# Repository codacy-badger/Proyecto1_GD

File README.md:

<p align="center"><p>

&nbsp;&nbsp;&nbsp;&nbsp;&nbsp;&nbsp;&nbsp;&nbsp;&nbsp;&nbsp;&nbsp;&nbsp;&nbsp;&nbsp;&nbsp;&nbsp;&nbsp;&nbsp;&nbsp;&nbsp;&nbsp;&nbsp;&nbsp;&nbsp;&nbsp;&nbsp;&nbsp;&nbsp;&nbsp;

&nbsp;&nbsp;&nbsp;&nbsp;&nbsp;&nbsp;&nbsp;&nbsp;&nbsp;&nbsp;&nbsp;&nbsp;&nbsp;&nbsp;&nbsp;&nbsp;&nbsp;&nbsp;&nbsp;&nbsp;&nbsp;&nbsp;&nbsp;&nbsp;&nbsp;&nbsp;&nbsp;&nbsp;&nbsp;&nbsp;&nbsp;&nbsp;&nbsp;

<!--  -->

# Proyecto1_GD
Proyecto en desarrollo, a continuación se describen las carpetas incluidas en el proyecto:

```
Proyecto1_GD
| .gitignore
| CONTRIBUTING.md
| LICENSE.md
| Manual.md
| README.md
|-- Archivos
|-- PlayGround
|-- Proyecto_A
|-- Proyecto_B
|-- Proyecto_C
|-- Proyecto_GUI
|-- Recursos
    |-- audio
    |-- imagenes
```

### 1. Archivos
Aqui incluiremos todos los archivos que aporten documentación al desarrollo, todos los archivos con formato *.docx* o *.pdf* dentro de la carpeta correspondiente al proyecto.

### 2.  PlayGround
Aqui cada uno puede incluir programas de prueba o borradores dentro de su carpeta correspondiente. Estos programas no pertenecen a la versión final del proyecto.

### 3. Proyecto A
Aquí incluiremos todo lo relacionado al desarrollo del [Proyecto A](./Proyecto_A), código, fichas técnicas y planos.

### 4. Proyecto B
Aquí incluiremos todo lo relacionado al desarrollo del Proyecto B, código, fichas técnicas y planos.
Este proyecto aún no esta definido.

### 5. Proyecto C
Aquí incluiremos todo lo relacionado al desarrollo del Proyecto C, código, fichas técnicas y planos.
Este proyecto aún no esta definido.

### 6. Proyecto GUI
Desarrollo de un Interfaz Gráfico.

#### Recursos
Aquí incluiremos principalmente imágenes de apoyo para las descripciones adicionales en los archivos README.md.

#### Extras
- Manual de uso [aquí](./Manual.md).
- Pautas de contribuyente [aquí](./CONTRIBUTING.md).

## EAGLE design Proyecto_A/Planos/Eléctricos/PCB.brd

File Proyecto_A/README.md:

<p align="center"><p>

# Proyecto A

```
|-- Proyecto_A
    |-- ADXL362
    |-- BMA400
    |-- Fichas_Técnicas
    |-- Planos
        |-- Mecánicos
        |-- Eléctricos
    |-- XBee
```

## Descripción

#### Sensores
- ADXL362 (MEMS Acelerómetro)
- BMA400 (Acelerómetro - BOSCH)
- MPU6050 (3 Acelerómetros y 3 giróscopos)

#### Microcontrolador (uC)
- MSP430 - Texas Instruments

#### Transmisor Tx/Rx
- XBee

#### Sensor x *N*

## 1. Fichas Técnicas
En esta carpeta podemos guardar todas las fichas técnicas relacionadas al proyecto.

## 2. Planos
En esta carpeta, se debe tener separado los planos mecánicos y eléctricos relacionados al proyecto. Incluir todos los planos sobre un mismo elemento dentro de una carpeta e incluir una descripción breve del contenido en un archivo MarkDown(.md)

#### 1. Mecánicos
Planos del encapsulado para los elementos electrónicos.

#### 2. Eléctricos
Planos del circuito impreso (PCB).
- Placa A
- Placa B

- uC+Xbee+MPU6050
- Modelo ATMEGA328P-AU+MPU+XBEE3: 20mm*28mm
<p align="center"><p>

- ATMEGA328P-AU+MPU6050+XBEE3, Size: 20mm*28mm
<p align="center"><p>

- ATMEGA328P-MU+MPU+XBEE3: Size: 21mm*27mm
<p align="center">

<p>

- MPU+XBEE3: Size: 18mm*28mm
<p align="center">

<p>

- 1: PCB: ADXLE362 [SPI] + uC + XBee3
- 2: PCB: BMA400 [I2C] + uC + XBee3
- 3: PCB: BMI270 [I2C] + uC + XBee3

#### Ubicación de los sensores
Las medidas de la cavidad donde iría el circuito es de 15mmx7mm y la profundidad es de 20mm.
<p align="center"><p>
<p align="center"><p>

En la siguiente foto se muestra el Xbee3 junto con su antena en una cavidad.
<p align="center"><p>

##### Sensores
- [Sensores de Vibración](https://faire-ca-soi-meme.fr/domotique/2018/09/03/test-xiaomi-aqara-vibration-sensor/)
- [Sensor de Humedad](https://faire-ca-soi-meme.fr/hack/2017/02/27/hack-xiaomi-mi-smart-temperature-and-humidity-sensor/)
- [MSP430](http://www.ti.com/product/MSP430G2553/technicaldocuments)
- [MSP-EXP43G2](https://www.mouser.pe/ProductDetail/Texas-Instruments/MSP-EXP430G2?qs=CLImetaeaXWH2pYG%252BA%252B4Vw%3D%3D)
- [MIKROE-3149](https://www.mouser.pe/ProductDetail/Mikroe/MIKROE-3149?qs=sGAEpiMZZMve4%2FbfQkoj%252BEPi4ApqHNF8CEaaCJoKqNM%3D)
- [BMA400](https://ae-bst.resource.bosch.com/media/_tech/media/datasheets/BST-BMA400-DS000.pdf)

##### Baterías
- [Li-Po Battery 3.7V 100mAh](https://es.aliexpress.com/item/4000670261171.html?spm=a2g0o.productlist.0.0.361999f3FETcJP&algo_pvid=44eadfe1-7417-4d6e-ab31-6dcf0ca93a4d&algo_expid=44eadfe1-7417-4d6e-ab31-6dcf0ca93a4d-19&btsid=0ab6d70515831768332806760e5465&ws_ab_test=searchweb0_0,searchweb201602_,searchweb201603_)
- [Energizer CR2032](https://data.energizer.com/pdfs/cr2032.pdf)

##### Algunos links importantes
- [Motion Metrics](https://www.motionmetrics.com/)
- [Mouser](www.mouser.com)
- [Digikey](https://www.digikey.com/)
- [Kivy](https://kivy.org/#home)
- [Micropython para pycharm](https://plugins.jetbrains.com/plugin/12445-xbee-micropython)
- [Diacsa](http://www.diacsa.com/servicios.html#)
- [Módulo de comunicación Digi XBee3](https://www.digi.com/products/models/xb3-24z8um-j)

##### Videos
- [MSP430](https://www.youtube.com/watch?v=dL2YPS96L18)
- [STM32 + MPU-6050](https://www.youtube.com/watch?v=ImctYI8hgq4)

```
output = - Accel x: 64780
- Accel y: 65148
- Accel z: 64808
- Gyro x: 64808
- Gyro y: 64824
- Gyro z: 64824
```
##### Extras
- [mpu6050](https://github.com/m-rtijn/mpu6050/blob/master/mpu6050/mpu6050.py)
- [Arduino-mpu6050](https://github.com/mattzzw/Arduino-mpu6050)

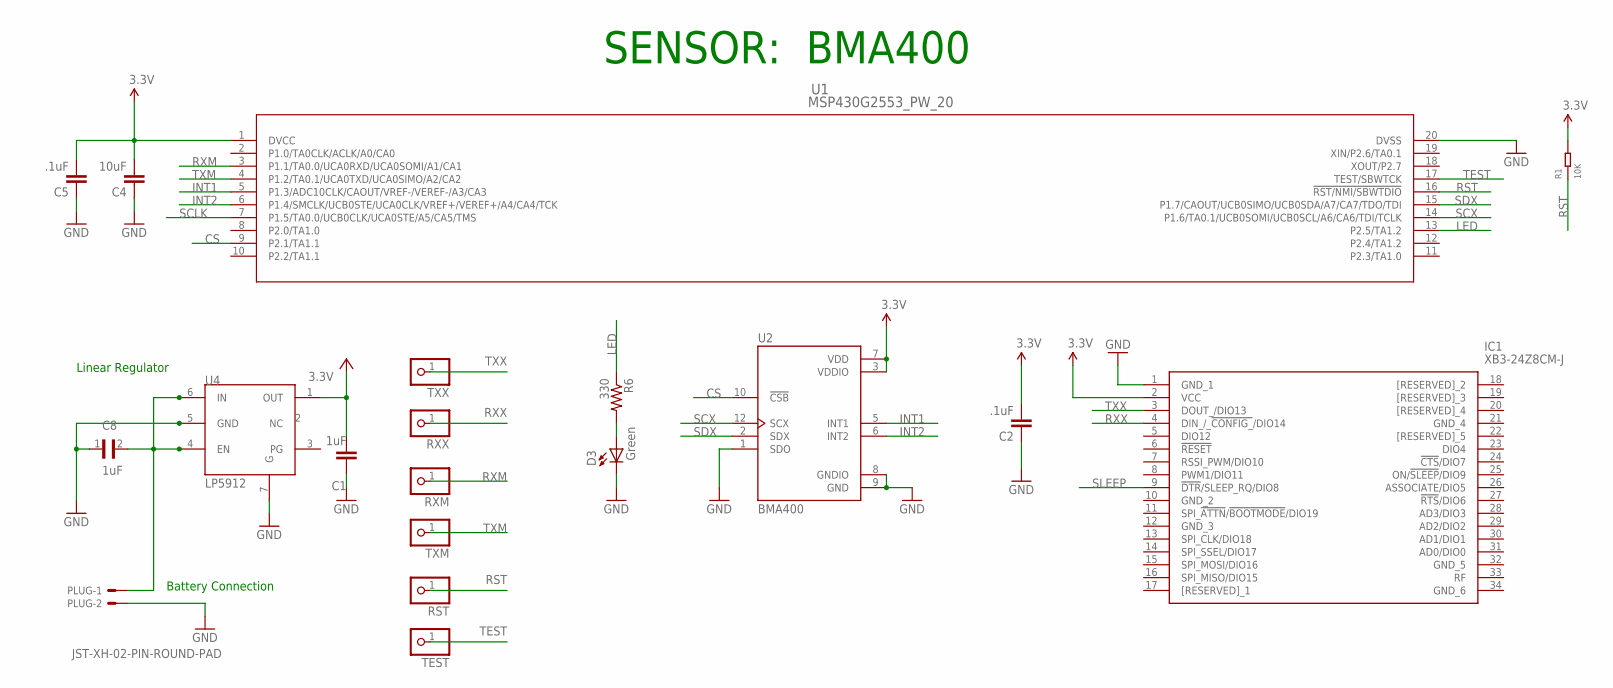
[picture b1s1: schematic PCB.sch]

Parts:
C1: 1uF; C0603
C2, C5: .1uF; 0603-CAP
C4: 10uF; 0603-CAP
C8: 1uF; CAPC1005X71N
D3: Green; 0603-LED-ALT1
IC1: XB3-24Z8CM-J; XB324Z8CMJ
PLUG: JST-XH-02-PIN-ROUND-PAD; JST-XH-02-PACKAGE-ROUND-PAD
R1: 10K; R0402
R6: 330; 0603-RES
RST: PINHD-1X1; 1X01
RXM: PINHD-1X1; 1X01
RXX: PINHD-1X1; 1X01
TEST: PINHD-1X1; 1X01
TXM: PINHD-1X1; 1X01
TXX: PINHD-1X1; 1X01
U1: MSP430G2553_PW_20; PW20
U2: BMA400; XDCR_BMA400
U4: LP5912

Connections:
3.3V: C2.2, C4.2, C5.2, IC1.2 (VCC), R1.2, U1.1 (DVCC), U2.3 (VDDIO), U2.7 (VDD)
BATTERY: C8.2, PLUG.1, U4.4 (EN), U4.6 (IN)
CS: U1.9 (P2.1/TA1.1), U2.10 (!CSB)
GND: C1.1, C2.1, C4.1, C5.1, C8.1, D3.C, IC1.1 (GND_1), PLUG.2, U1.20 (DVSS), U2.1 (SDO), U2.8 (GNDIO), U2.9 (GND), U4.5 (GND), U4.7 (G)
INT1: U1.5 (P1.3/ADC10CLK/CAOUT/VREF-/VEREF-/A3/CA3), U2.5 (INT1)
INT2: U1.6 (P1.4/SMCLK/UCB0STE/UCA0CLK/VREF+/VEREF+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), U2.6 (INT2)
LED: R6.1, U1.13 (P2.5/TA1.2)
unnamed: D3.A, R6.2
RST: R1.1, RST.1, U1.16 (!RST/NMI/SBWTDIO)
RXM: RXM.1, U1.3 (P1.1/TA0.0/UCA0RXD/UCA0SOMI/A1/CA1)
RXX: IC1.4 (DIN_/_!CONFIG_!/DIO14), RXX.1
SCLK: U1.7 (P1.5/TA0.0/UCB0CLK/UCA0STE/A5/CA5/TMS)
SCX: U1.14 (P1.6/TA0.1/UCB0SOMI/UCB0SCL/A6/CA6/TDI/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), U2.12 (SCX)
SDX: U1.15 (P1.7/CAOUT/UCB0SIMO/UCB0SDA/A7/CA7/TDO/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), U2.2 (SDX)
SLEEP: IC1.9 (!DTR!/SLEEP_RQ/DIO8)
TEST: TEST.1, U1.17 (TEST/SBWTCK)
TXM: TXM.1, U1.4 (P1.2/TA0.1/UCA0TXD/UCA0SIMO/A2/CA2)
TXX: IC1.3 (DOUT_/DIO13), TXX.1
VCC: C1.2, U4.1 (OUT)

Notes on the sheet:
Linear Regulator
Battery Connection
SENSOR: BMA400

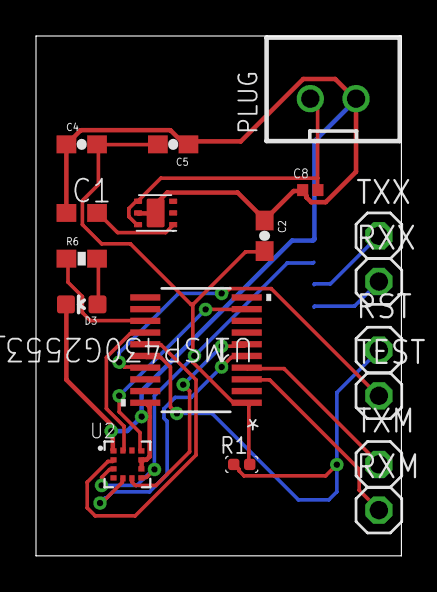
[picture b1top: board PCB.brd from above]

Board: 2 copper layers, 20.3 x 28.9 mm, 19 parts (1 on the bottom side), 17 nets.

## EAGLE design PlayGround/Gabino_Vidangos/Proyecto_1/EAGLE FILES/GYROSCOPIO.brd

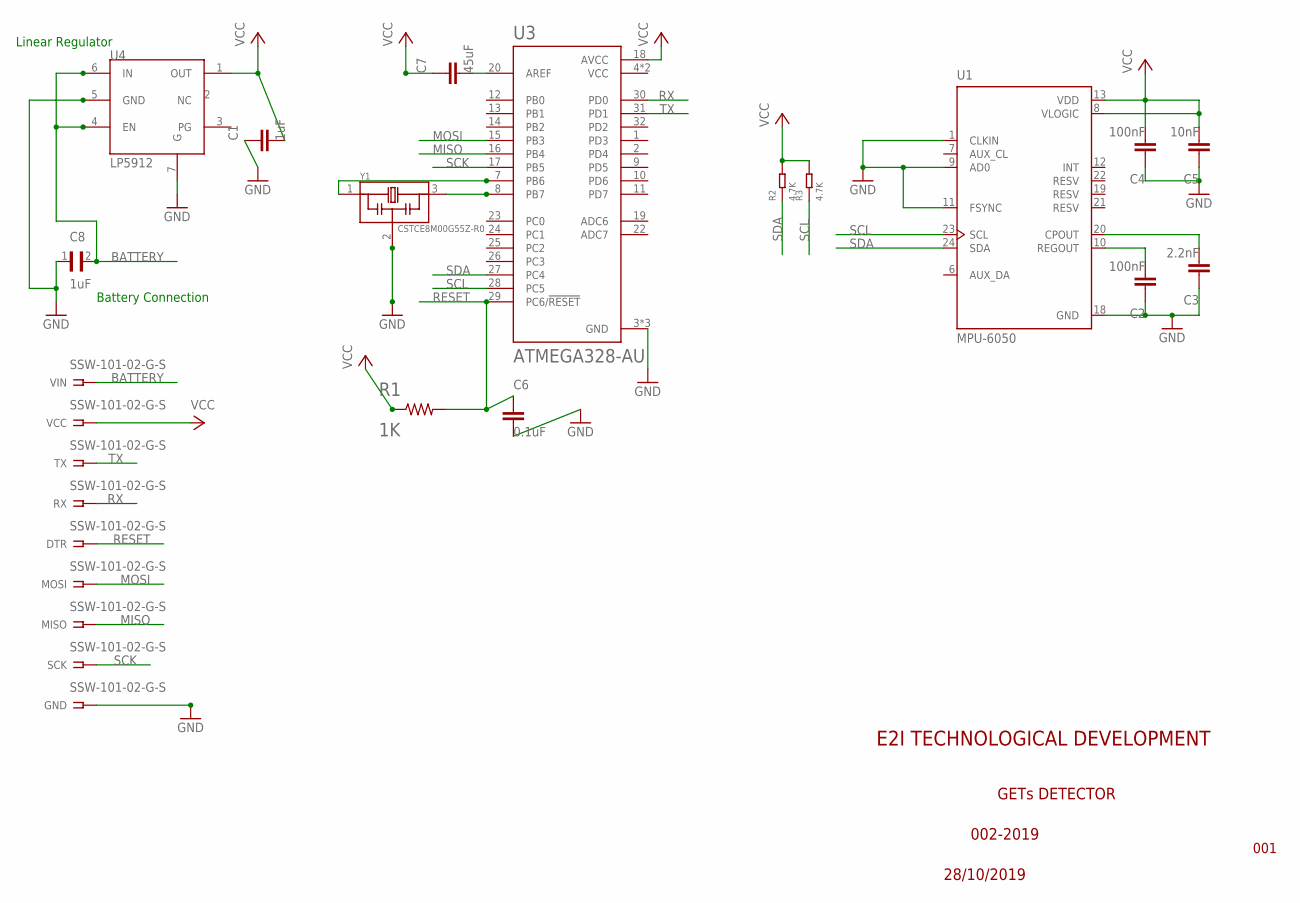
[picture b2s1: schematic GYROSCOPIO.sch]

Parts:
C1: 1uF; C0603
C2, C4: 100nF; C0603
C3: 2.2nF; C0603
C5: 10nF; C0603
C6: 0.1uF; C0603
C7: 45uF; C0603
C8: 1uF; CAPC1005X71N
DTR: SSW-101-02-G-S
GND: SSW-101-02-G-S
MISO: SSW-101-02-G-S
MOSI: SSW-101-02-G-S
R1: 1K; R0603
R2, R3: 4.7K; R0402
RX: SSW-101-02-G-S
SCK: SSW-101-02-G-S
TX: SSW-101-02-G-S
U1: MPU-6050; QFN50P400X400X95-24N
U3: ATMEGA328-AU; QFP80P900X900X120-32N
U4: LP5912
VCC: SSW-101-02-G-S
VIN: SSW-101-02-G-S
Y1: CSTCE8M00G55Z-R0; OSC_CSTCE16M0V53-R0

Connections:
BATTERY: C8.2, U4.4 (EN), U4.6 (IN), VIN.1
GND: C1.1, C2.1, C3.1, C4.1, C5.1, C6.2, C8.1, GND.1, U1.1 (CLKIN), U1.9 (AD0), U1.11 (FSYNC), U1.18 (GND), U3.3 (GND), U3.5 (GND), U3.21 (GND), U4.5 (GND), U4.7 (G), Y1.2
MISO: MISO.1, U3.16 (PB4)
MOSI: MOSI.1, U3.15 (PB3)
unnamed: U3.7 (PB6), Y1.1
unnamed: U3.8 (PB7), Y1.3
unnamed: C2.2, U1.10 (REGOUT)
unnamed: C3.2, U1.20 (CPOUT)
unnamed: C7.2, U3.20 (AREF)
RESET: C6.1, DTR.1, R1.2, U3.29 (PC6/!RESET)
RX: RX.1, U3.30 (PD0)
SCK: SCK.1, U3.17 (PB5)
SCL: R3.1, U1.23 (SCL), U3.28 (PC5)
SDA: R2.1, U1.24 (SDA), U3.27 (PC4)
TX: TX.1, U3.31 (PD1)
VCC: C1.2, C4.2, C5.2, C7.1, R1.1, R2.2, R3.2, U1.8 (VLOGIC), U1.13 (VDD), U3.4 (VCC), U3.6 (VCC), U3.18 (AVCC), U4.1 (OUT), VCC.1

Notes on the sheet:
Linear Regulator
Battery Connection
GETs DETECTOR
002-2019
28/10/2019
001
E2I TECHNOLOGICAL DEVELOPMENT

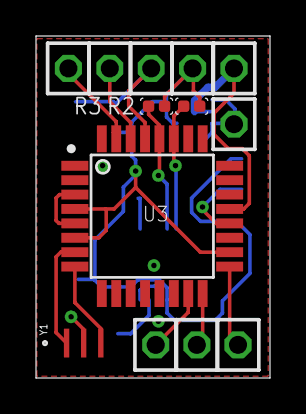
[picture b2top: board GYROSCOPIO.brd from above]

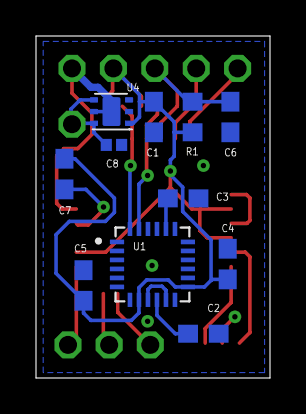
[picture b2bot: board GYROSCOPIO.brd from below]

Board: 2 copper layers, 13.0 x 19.0 mm, 24 parts (11 on the bottom side), 16 nets.

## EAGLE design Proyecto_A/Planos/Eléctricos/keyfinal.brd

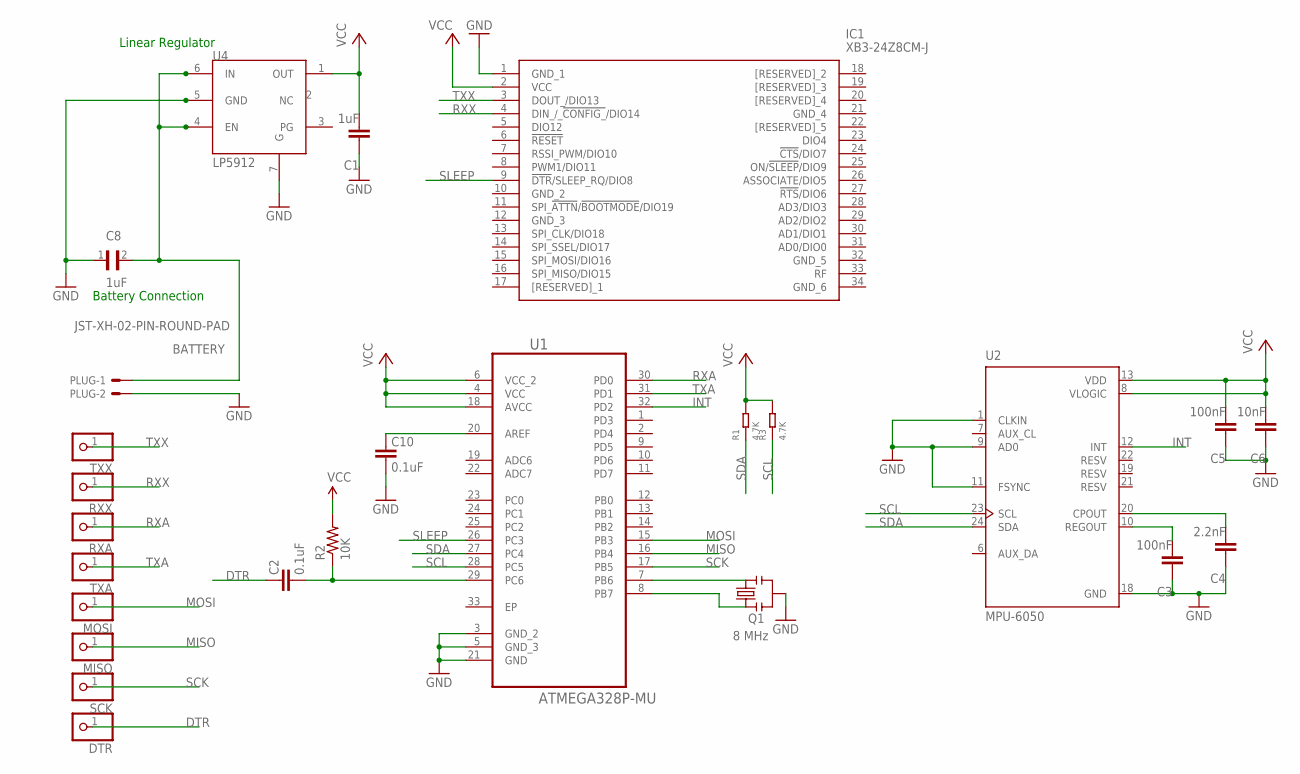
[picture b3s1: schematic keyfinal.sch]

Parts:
C1: 1uF; C0603
C2, C10: 0.1uF; 0603-CAP
C3, C5: 100nF; C0603
C4: 2.2nF; C0603
C6: 10nF; C0603
C8: 1uF; CAPC1005X71N
DTR: DTR; 1X01
IC1: XB3-24Z8CM-J; XB324Z8CMJ
MISO: PINHD-1X1; 1X01
MOSI: PINHD-1X1; 1X01
PLUG: JST-XH-02-PIN-ROUND-PAD; JST-XH-02-PACKAGE-ROUND-PAD
Q1: 8 MHz; RESONATOR-SMD-1:1
R1, R3: 4.7K; R0402
R2: 10K; 0603-RES
RXA: PINHD-1X1; 1X01
RXX: PINHD-1X1; 1X01
SCK: PINHD-1X1; 1X01
TXA: PINHD-1X1; 1X01
TXX: PINHD-1X1; 1X01
U1: ATMEGA328P-MU; QFN50P500X500X100-33N
U2: MPU-6050; QFN50P400X400X95-24N
U4: LP5912

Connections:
BATTERY: C8.2, PLUG.1, U4.4 (EN), U4.6 (IN)
DTR: C2.2, DTR.1
GND: C1.1, C3.1, C4.1, C5.1, C6.1, C8.1, C10.1, IC1.1 (GND_1), PLUG.2, Q1.2, U1.3 (GND_2), U1.5 (GND_3), U1.21 (GND), U2.1 (CLKIN), U2.9 (AD0), U2.11 (FSYNC), U2.18 (GND), U4.5 (GND), U4.7 (G)
INT: U1.32 (PD2), U2.12 (INT)
MISO: MISO.1, U1.16 (PB4)
MOSI: MOSI.1, U1.15 (PB3)
unnamed: C10.2, U1.20 (AREF)
unnamed: Q1.3, U1.7 (PB6)
unnamed: C3.2, U2.10 (REGOUT)
unnamed: C4.2, U2.20 (CPOUT)
unnamed: Q1.1, U1.8 (PB7)
RESET1: C2.1, R2.1, U1.29 (PC6)
RXA: RXA.1, U1.30 (PD0)
RXX: IC1.4 (DIN_/_!CONFIG_!/DIO14), RXX.1
SCK: SCK.1, U1.17 (PB5)
SCL: R3.1, U1.28 (PC5), U2.23 (SCL)
SDA: R1.1, U1.27 (PC4), U2.24 (SDA)
SLEEP: IC1.9 (!DTR!/SLEEP_RQ/DIO8), U1.26 (PC3)
TXA: TXA.1, U1.31 (PD1)
TXX: IC1.3 (DOUT_/DIO13), TXX.1
VCC: C1.2, C5.2, C6.2, IC1.2 (VCC), R1.2, R2.2, R3.2, U1.4 (VCC), U1.6 (VCC_2), U1.18 (AVCC), U2.8 (VLOGIC), U2.13 (VDD), U4.1 (OUT)

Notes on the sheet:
Linear Regulator
Battery Connection

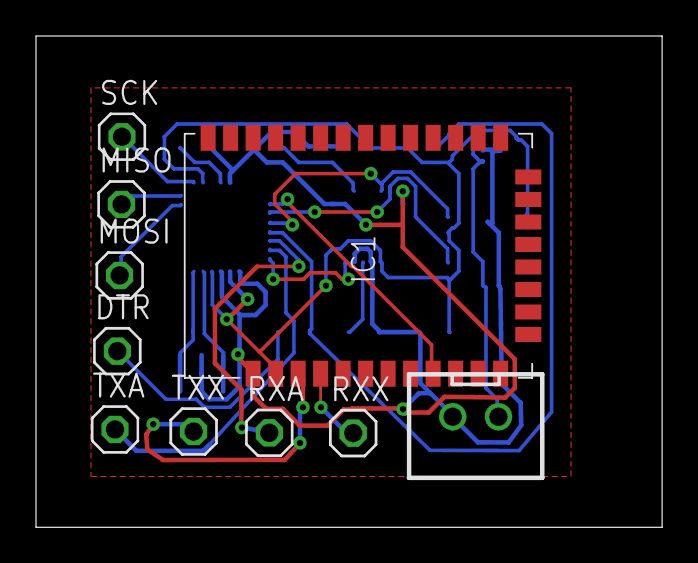
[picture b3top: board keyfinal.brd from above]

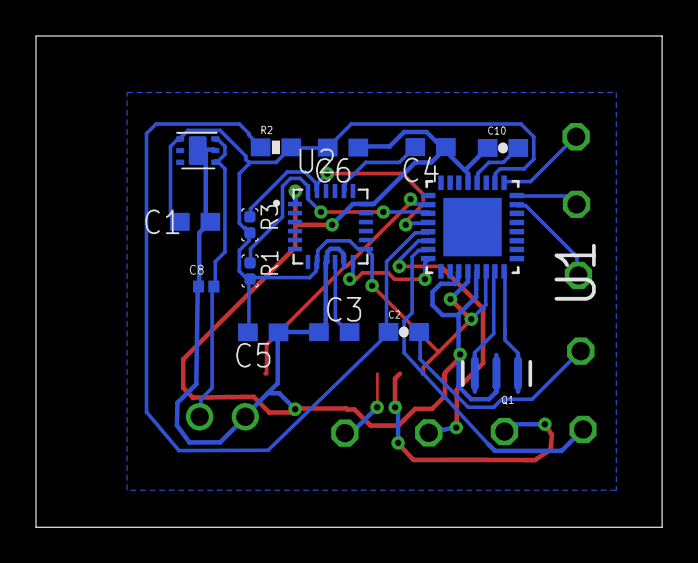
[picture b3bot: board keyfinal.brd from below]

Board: 2 copper layers, 34.8 x 27.3 mm, 25 parts (15 on the bottom side), 21 nets.

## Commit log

2020-02-18 Manual.md ha sido creado.
2020-02-18 La carpeta de Imagenes ha sido creada.
2020-02-18 Se han editado Manual y Readme.
2020-02-18 Logo ha sido agregado.
2020-02-18 Mejorar Readme.md
2020-02-18 Update Shield
2020-02-18 Se ha creado TestKivy
2020-02-18 Se muestra imagen en el README.md
2020-02-18 Agrandar imagen.
2020-02-18 Se ha agregado la Documentacion de las pruebas.
2020-02-18 Link al Tutorial ha sido creado
2020-03-25 Create XBeeProtocol
2020-03-25 testXBee ha sido creado.
2020-03-27 Create ADLX360
2020-03-28 ADXL362
2020-03-28 ADLX362
2020-03-28 Cambios hechos para modificar carpetas
    Estos cambios fueron realizados para mejorar la organizacion del programa
2020-03-28 Actualización interrupcion
    Se añadieron funciones para manejar el registro FIFOCONTROL
2020-03-30 Create Documentos
2020-04-02 prueba
2020-04-02 Programa ADLX
2020-04-06 Agregado el sensor del BMA
    Programa del sensor BMA400 con simple reading
2020-04-06 Test
2020-04-07 Eliminar archivos basura
2020-04-07 Update ADXL362_Activacion_de_movimiento.ino
    En sensor despierta a la placa y manda datos cuando se presenta un movimiento ; a la ausencia de movimiento la placa entra en modo bajo consumo.
2020-04-07 Update ADXL362_Activacion_de_movimiento.ino
    Se arreglo de bug de toma de datos y se implemento de modo bajo de consumo en la placa
2020-04-08 Se ha creado licencia y pautas de contribuyente.
2020-04-08 README.md ha sido editado.
2020-04-08 Update issue templates
2020-04-08 BMA400 INTERRUPTION
    Se realizó la interrupcion y el sleep del BMA400 basandose en el programa de ADLX.
2020-04-08 Se ha creado un plantilla para Pull Request.
2020-04-08 codeStyle
2020-04-08 Pautas de contribuyente.
2020-04-08 Eliminando archivos basura
2020-04-08 Ordenando archivos
2020-04-12 Reorganización de todo el proyecto.
2020-04-12 Problemas solucionados despues del Merge.
2020-04-12 Cambio de nombre a Recursos.
2020-04-12 Update Readme.
2020-04-13 README.md update
2020-04-16 Organizando el código
2020-04-16 Organizing code
2020-04-16 Se ha copiado la carpeta SimpleReading.
2020-04-22 Implementacion deteccion
    Se implementó la deteccion de cambio de movimiento y tambien un algoritmo de deteccion de caidas (Caida libre).
2020-05-27 BMI270 Reading
2020-06-22 Phyton
2020-06-22 Interfaz Xbee
    Interfaz Xbee
2020-06-25 Prueba5
    Código que combina MSPread, MQTT y modificacion de parametros
2020-06-25 BMA400Simulator

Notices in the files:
parts and their libraries:
SparkFun-Capacitors: Licensing: CC v3.0 Share-Alike You are welcome to use this library for commercial purposes.
